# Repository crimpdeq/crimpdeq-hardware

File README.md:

# Crimpdeq Hardware

The Crimpdeq hardware is actively evolving. Several people have already built a prototype. Instructions for building your own prototype are available in the [Crimpdeq book](crimpdeq.github.io/book/). In parallel, I'm designing a PCB that is nearly finished but not yet manufactured, so it remains untested.

## Prototype

Here is the prototype:

The [Making Your Own Crimpdeq](https://crimpdeq.github.io/book/assembly.html) chapter explains the required materials and steps to build your own Crimpdeq.

## PCB

The PCB design is located under `hardware/crimpdeq/` and was created using KiCad. It is a two-layer board based on the [Rust ESP Board](https://github.com/esp-rs/esp-rust-board). This design removes unused sensors from the original board and adds the necessary components for this project.

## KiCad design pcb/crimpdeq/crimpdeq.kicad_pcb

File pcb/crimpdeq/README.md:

# Crimpdeq — 30 x 30 mm Four-Layer Design

This is the repository's single canonical PCB design and current production candidate. It
includes corrected ESP32 module grounding, an ADS1220 load-cell front-end, and compact
power/USB routing.

- Board/project/rules/schematic: `crimpdeq.{kicad_pcb,kicad_pro,kicad_dru,kicad_sch}`
- Outline: 30.00 x 30.00 mm (30.05 x 30.05 mm including edge stroke)
- Components: 55 total, 36 front / 19 back
- U1 antenna and D4 LED: back; J2 USB-C and U3 ADS1220: front
- U1 pins 37–53, including EPAD 49, are connected to GND as required by Espressif.
- R20/R21/R22 provide 10 kΩ pull-ups for SDA, SCL, and the MAX17048 alert output.
- U3 ADS1220 (TSSOP-16, LCSC C48263) uses ratiometric +3V3 excitation (E+/REFP0) with
  E-/REFN0 on GND. AVDD/DVDD decoupling is C11 + C19. R7/R8/C12 filter into AIN0/AIN1.
- SPI map: GPIO5 SCK, GPIO4 MOSI, GPIO3 CS, GPIO1 MISO (DOUT/~DRDY). CLK is grounded.
- The buck input, switch, output, and feedback components form a compact front-side cluster.
- Twelve dedicated GND stitching vias tie the outer floods to the solid L2 plane.
- All four load-cell pads (`E-`, `A-`, `A+`, `E+`) are together on the bottom edge near U3 and
  away from the antenna. `B+` and `SW` are on the right edge.
- The ESP32 antenna body overhangs the top edge; its all-layer copper keepout is retained.
- The USB-C housing overhangs the bottom edge by 1.00 mm; connector copper remains in-board.
- L2 is a signal-free GND plane. L3 carries the 3V3 pour and low-speed signals.
- KiCad error-level DRC: zero violations and zero unconnected items.
- Schematic ERC and PCB/schematic parity: zero errors.

Production files:

- Gerbers: `gerbers/crimpdeq.zip`
- Assembly package: `assembly/`

Manufacturer DFM review and physical validation of power integrity, USB, ADS1220 noise, antenna
performance, and connector fit remain required before production.

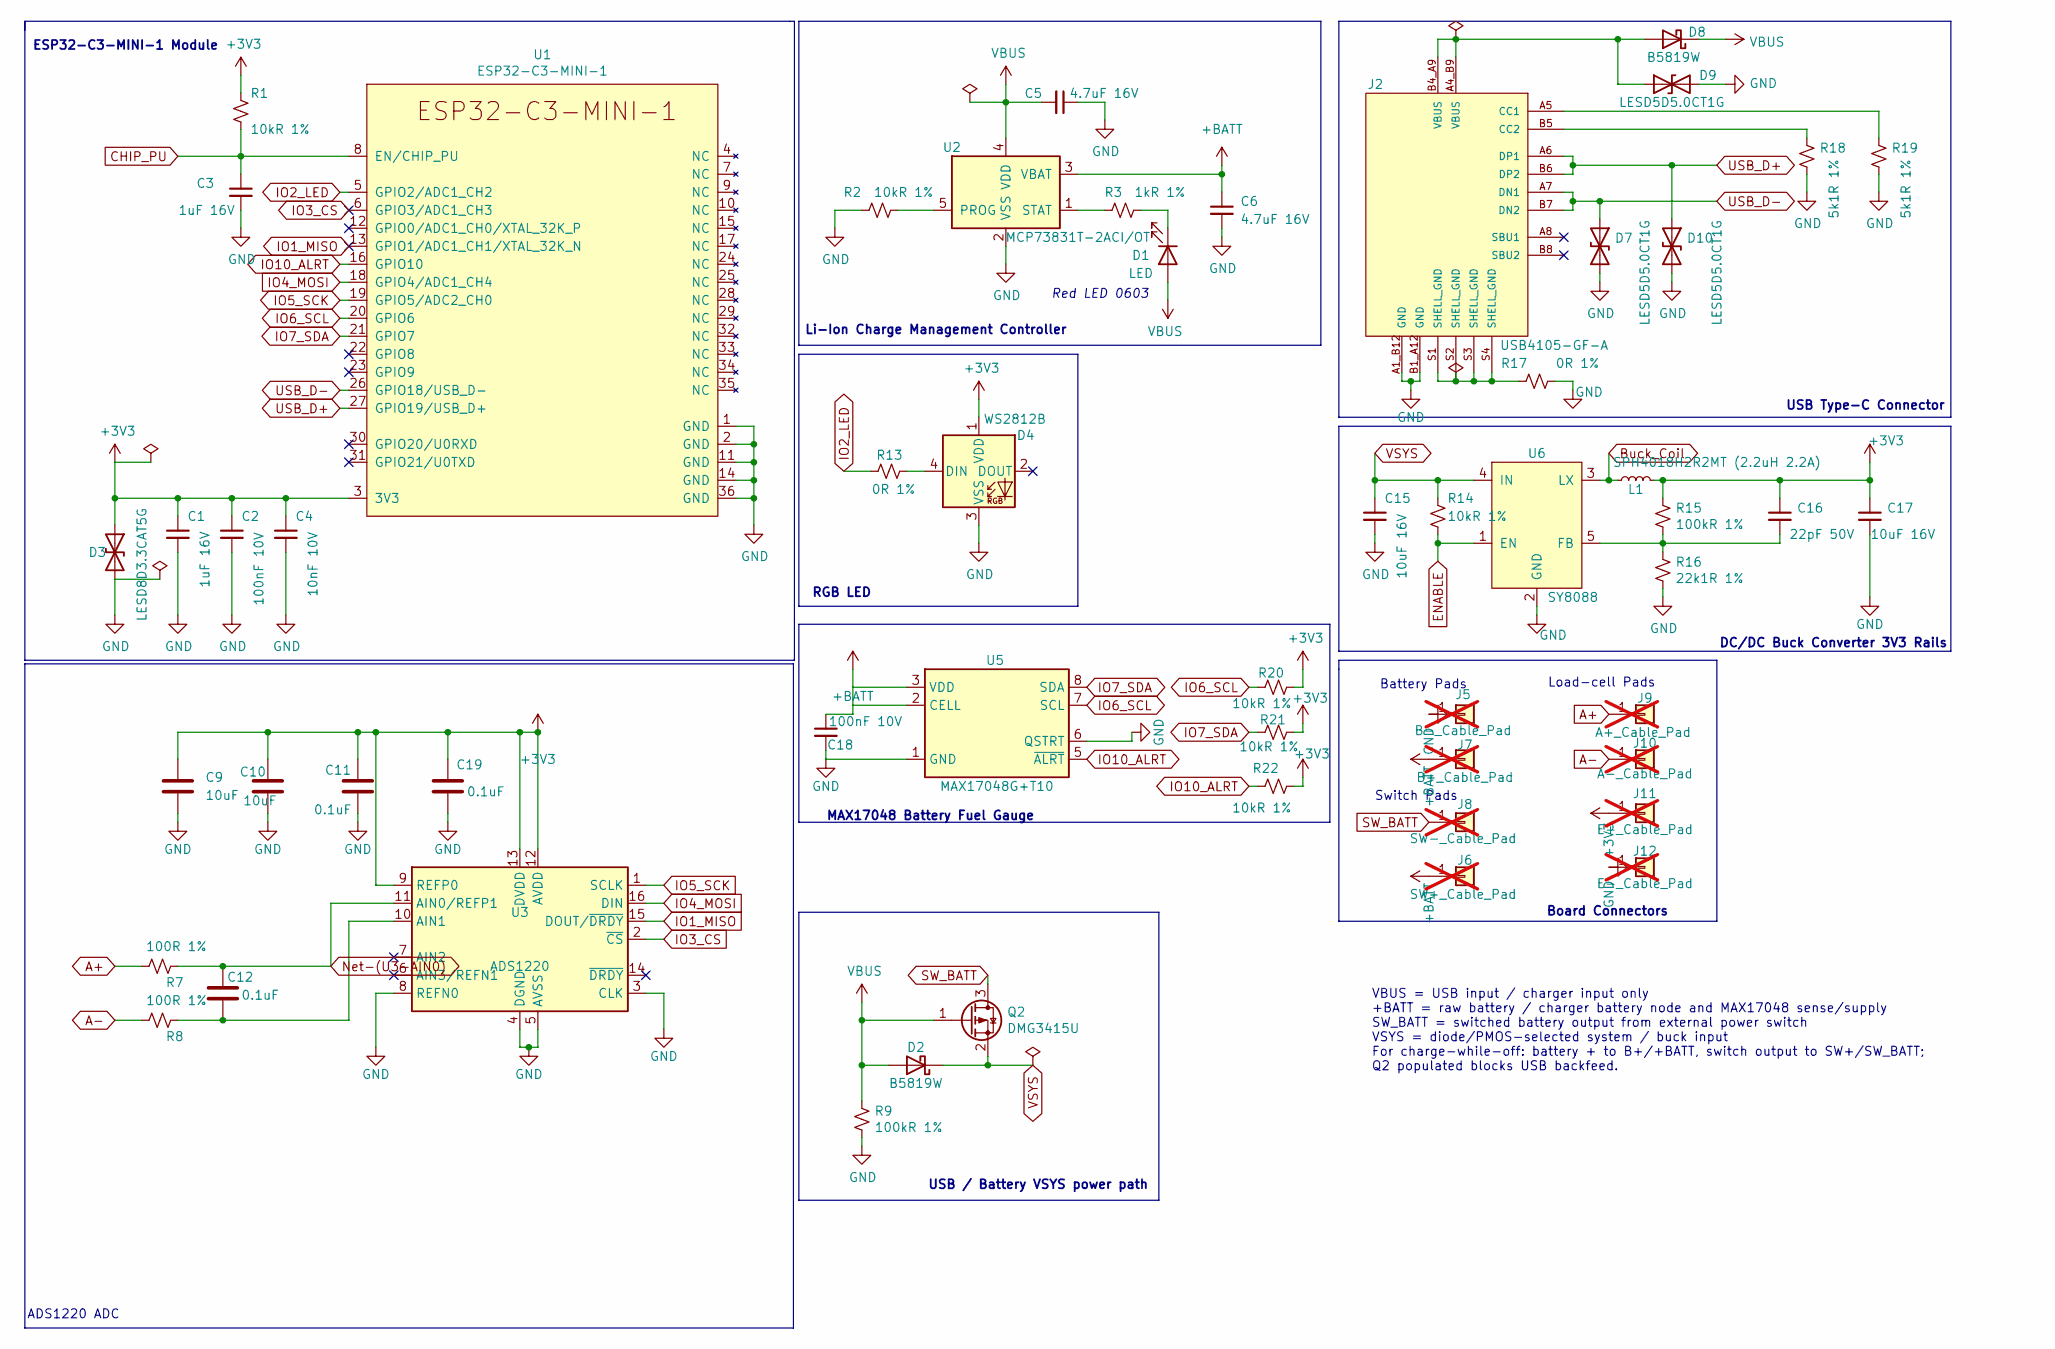
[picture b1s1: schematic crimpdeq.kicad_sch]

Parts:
C1, C3: 1uF 16V; C_0402_1005Metric; LCSC C52923
C2: 100nF 10V; C_0402_1005Metric; LCSC C1525
C4: 10nF 10V; C_0402_1005Metric; LCSC C15195
C5, C6: 4.7uF 16V; C_0603_1608Metric; LCSC C19666
C9, C10: 10uF; C_0603_1608Metric
C11, C12, C19: 0.1uF; C_0603_1608Metric
C15, C17: 10uF 16V; C_0805_2012Metric; LCSC C15850
C16: 22pF 50V; C_0603_1608Metric; LCSC C1653
C18: 100nF 10V; C_0402_1005Metric
D1: LED; LED_0603_1608Metric; LCSC C2286
D2, D8: B5819W; D_SOD-123; LCSC C8598
D3: LESD8D3.3CAT5G; D_SOD-882; LCSC C172409
D4: WS2812B; LED_WS2812B_PLCC4_5.0x5.0mm_P3.2mm
D7, D9, D10: LESD5D5.0CT1G; D_SOD-523; LCSC C383211
J2: USB4105-GF-A; GCT_USB4105-GF-A; PARTREV A3; LCSC C165948
J5: B-_Cable_Pad; TestPoint_THTPad_D1.5mm_Drill0.7mm; not fitted
J6: SW+_Cable_Pad; TestPoint_THTPad_D1.5mm_Drill0.7mm; not fitted
J7: B+_Cable_Pad; TestPoint_THTPad_D1.5mm_Drill0.7mm; not fitted
J8: SW-_Cable_Pad; TestPoint_THTPad_D1.5mm_Drill0.7mm; not fitted
J9: A+_Cable_Pad; TestPoint_THTPad_D1.5mm_Drill0.7mm; not fitted
J10: A-_Cable_Pad; TestPoint_THTPad_D1.5mm_Drill0.7mm; not fitted
J11: E+_Cable_Pad; TestPoint_THTPad_D1.5mm_Drill0.7mm; not fitted
J12: E-_Cable_Pad; TestPoint_THTPad_D1.5mm_Drill0.7mm; not fitted
L1: SPH4018H2R2MT (2.2uH 2.2A); L_Bourns-SRN4018; LCSC C370436
Q2: DMG3415U; SOT-23; LCSC C96616
R1, R2, R14: 10kR 1%; R_0402_1005Metric; LCSC C25744
R3: 1kR 1%; R_0402_1005Metric; LCSC C11702
R7, R8: 100R 1%; R_0402_1005Metric; LCSC C25076
R9, R15: 100kR 1%; R_0402_1005Metric; LCSC C25741
R13: 0R 1%; R_0402_1005Metric; LCSC C25744
R16: 22k1R 1%; R_0402_1005Metric; LCSC C43473
R17: 0R 1%; R_0402_1005Metric; LCSC C17168
R18, R19: 5k1R 1%; R_0402_1005Metric; LCSC C25905
R20, R21, R22: 10kR 1%; R_0402_1005Metric; LCSC C60490
U1: ESP32-C3-MINI-1; LCSC C2838502
U2: MCP73831T-2ACI/OT; SOT-23-5; LCSC C424093
U3: ADS1220; TSSOP-16_4.4x5mm_P0.65mm
U5: MAX17048G+T10; TDFN-8-1EP_2x2mm_P0.5mm_EP0.8x1.2mm
U6: SY8088; SOT-23-5; LCSC C479072

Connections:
+3V3: C1.1, C2.1, C4.1, C9.1, C10.1, C11.1, C16.1, C17.1, C19.1, D3.1 (A1), D4.1 (VDD), J11.1, L1.2, R1.1, R15.1, R20.2, R21.2, R22.2, U1.3 (3V3), U3.9 (REFP0), U3.12 (AVDD), U3.13 (DVDD)
+BATT: C6.1, C18.1, J6.1 (Pin_1_1), J7.1 (Pin_1_1), U2.3 (VBAT), U5.2 (CELL), U5.3 (VDD)
A+: J9.1 (Pin_1_1), R7.2
A-: J10.1 (Pin_1_1), R8.2
Buck_Coil: L1.1, U6.3 (LX)
CHIP_PU: C3.1, R1.2, U1.8 (EN/CHIP_PU)
ENABLE: R14.2, U6.1 (EN)
GND: C1.2, C2.2, C3.2, C4.2, C5.1, C6.2, C9.2, C10.2, C11.2, C15.2, C17.2, C18.2, C19.2, D3.2 (A2), D4.3 (VSS), D7.2 (A2), D9.2 (A2), D10.2 (A2), J2.A1_B12 (GND), J2.B1_A12 (GND), J5.1 (Pin_1_1), J12.1, R2.1, R9.2, R16.2, R17.2, R18.2, R19.2, U1.1 (GND), U1.2 (GND), U1.11 (GND), U1.14 (GND), U1.36 (GND), U1.37 (GND), U1.38 (GND), U1.39 (GND), U1.40 (GND), U1.41 (GND), U1.42 (GND), U1.43 (GND), U1.44 (GND), U1.45 (GND), U1.46 (GND), U1.47 (GND), U1.48 (GND), U1.49 (GND), U1.50 (GND), U1.51 (GND), U1.52 (GND), U1.53 (GND), U2.2 (VSS), U3.3 (CLK), U3.4 (DGND), U3.5 (AVSS), U3.8 (REFN0), U5.1 (GND), U5.4 (GND), U5.6 (QSTRT), U5.9 (GND), U6.2 (GND)
IO1_MISO: U1.13 (GPIO1/ADC1_CH1/XTAL_32K_N), U3.15 (DOUT/~DRDY)
IO2_LED: R13.1, U1.5 (GPIO2/ADC1_CH2)
IO3_CS: U1.6 (GPIO3/ADC1_CH3), U3.2 (~CS)
IO4_MOSI: U1.18 (GPIO4/ADC1_CH4), U3.16 (DIN)
IO5_SCK: U1.19 (GPIO5/ADC2_CH0), U3.1 (SCLK)
IO6_SCL: R20.1, U1.20 (GPIO6), U5.7 (SDA)
IO7_SDA: R21.1, U1.21 (GPIO7), U5.8 (SCL)
IO10_ALRT: R22.1, U1.16 (GPIO10), U5.5 (~ALRT)
unnamed: D1.1 (K), R3.2
unnamed: D4.4 (DIN), R13.2
unnamed: D8.2 (A), D9.1 (A1), J2.A4_B9 (VBUS), J2.B4_A9 (VBUS)
unnamed: J2.A5 (CC1), R19.1
unnamed: J2.B5 (CC2), R18.1
unnamed: J2.S1 (SHELL_GND), J2.S2 (SHELL_GND), J2.S3 (SHELL_GND), J2.S4 (SHELL_GND), R17.1
unnamed: R2.2, U2.5 (PROG)
unnamed: R3.1, U2.1 (STAT)
unnamed: C12.1, R7.1, U3.11 (AIN0/REFP1)
unnamed: C12.2, R8.1, U3.10 (AIN1)
unnamed: C16.2, R15.2, R16.1, U6.5 (FB)
SW_BATT: J8.1 (Pin_1_1), Q2.3 (D)
USB_D+: D10.1 (A1), J2.A6 (DP1), J2.B6 (DP2), U1.27 (GPIO19/USB_D+)
USB_D-: D7.1 (A1), J2.A7 (DN1), J2.B7 (DN2), U1.26 (GPIO18/USB_D-)
VBUS: C5.2, D1.2 (A), D2.2 (A), D8.1 (K), Q2.1 (G), R9.1, U2.4 (VDD)
VSYS: C15.1, D2.1 (K), Q2.2 (S), R14.1, U6.4 (IN)

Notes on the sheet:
ADS1220 ADC
USB Type-C Connector
Board Connectors
Li-Ion Charge Management Controller
USB / Battery VSYS power path
MAX17048 Battery Fuel Gauge
Red LED 0603
Load-cell Pads
Switch Pads
ESP32-C3-MINI-1 Module
RGB LED
DC/DC Buck Converter 3V3 Rails
Battery Pads
VBUS = USB input / charger input only +BATT = raw battery / charger battery node and MAX17048 sense/supply SW_BATT = switched battery output from external power switch VSYS = diode/PMOS-selected system / buck input For charge-while-off: battery + to B+/+BATT, switch output to SW+/SW_BATT; Q2 popula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

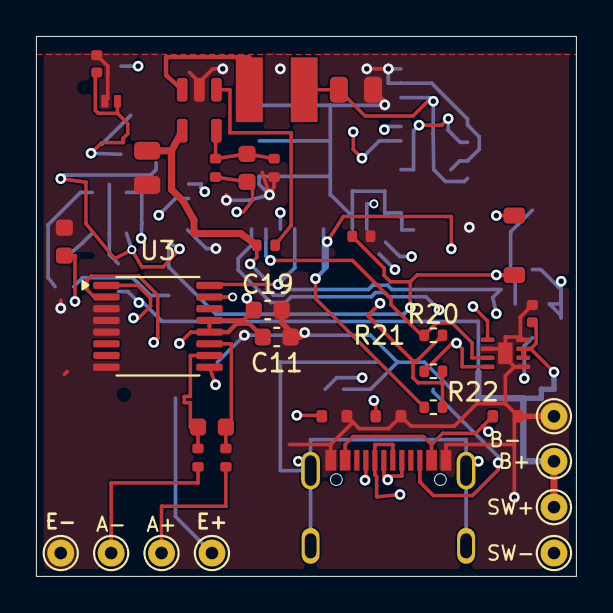
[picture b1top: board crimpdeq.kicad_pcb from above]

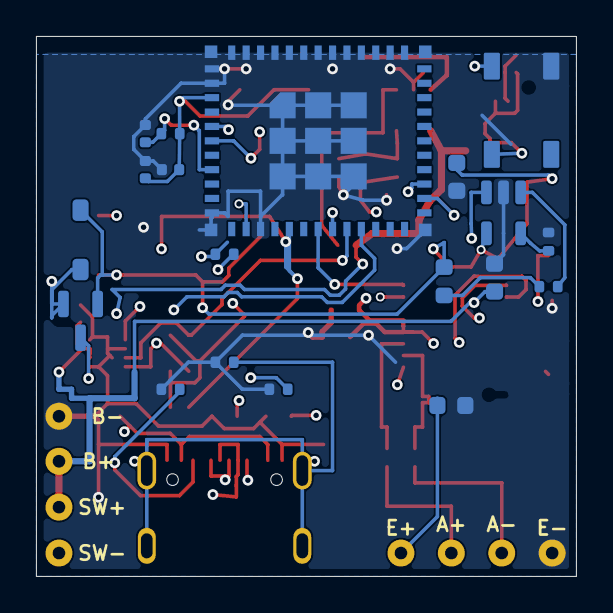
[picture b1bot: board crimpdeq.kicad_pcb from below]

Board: 4 copper layers, 30.0 x 30.0 mm, 55 parts (19 on the bottom side), 32 nets.

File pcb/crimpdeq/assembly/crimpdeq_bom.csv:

Item,Quantity,Designator,Value,Footprint,MPN,Type,Notes
1,2,"C1,C3",1uF 16V,C_0402_1005Metric,C52923,SMD,
2,2,"C2,C18",100nF 10V,C_0402_1005Metric,C1525,SMD,
3,1,C4,10nF 10V,C_0402_1005Metric,C15195,SMD,
4,2,"C5,C6",4.7uF 16V,C_0603_1608Metric,C19666,SMD,
5,2,"C9,C10",10uF,C_0603_1608Metric,C19702,SMD,
6,3,"C11,C12,C19",0.1uF,C_0603_1608Metric,C14663,SMD,
7,2,"C15,C17",10uF 16V,C_0805_2012Metric,C15850,SMD,
8,1,C16,22pF 50V,C_0603_1608Metric,C1653,SMD,
9,1,D1,LED,LED_0603_1608Metric,C2286,SMD,
10,2,"D2,D8",B5819W,D_SOD-123,C8598,SMD,
11,1,D3,LESD8D3.3CAT5G,D_SOD-882,C172409,SMD,
12,1,D4,WS2812B,LED_WS2812B_PLCC4_5.0x5.0mm_P3.2mm,C52917433,SMD,
13,3,"D7,D9,D10",LESD5D5.0CT1G,D_SOD-523,C2982332,SMD,
14,1,J2,USB4105-GF-A,GCT_USB4105-GF-A,C165948,Hybrid,PTH shell tabs; THT/manual soldering
15,1,J5,B-_Cable_Pad,TestPoint_THTPad_D1.5mm_Drill0.7mm,,THT,Do Not Place
16,1,J6,SW+_Cable_Pad,TestPoint_THTPad_D1.5mm_Drill0.7mm,,THT,Do Not Place
17,1,J7,B+_Cable_Pad,TestPoint_THTPad_D1.5mm_Drill0.7mm,,THT,Do Not Place
18,1,J8,SW-_Cable_Pad,TestPoint_THTPad_D1.5mm_Drill0.7mm,,THT,Do Not Place
19,1,J9,A+_Cable_Pad,TestPoint_THTPad_D1.5mm_Drill0.7mm,,THT,Do Not Place
20,1,J10,A-_Cable_Pad,TestPoint_THTPad_D1.5mm_Drill0.7mm,,THT,Do Not Place
21,1,J11,E+_Cable_Pad,TestPoint_THTPad_D1.5mm_Drill0.7mm,,THT,Do Not Place
22,1,J12,E-_Cable_Pad,TestPoint_THTPad_D1.5mm_Drill0.7mm,,THT,Do Not Place
23,1,L1,SPH4018H2R2MT (2.2uH 2.2A),L_Bourns-SRN4018,C370436,SMD,
24,1,Q2,DMG3415U,SOT-23,C96616,SMD,
25,6,"R1,R2,R14,R20,R21,R22",10kR 1%,R_0402_1005Metric,C60490,SMD,
26,1,R3,1kR 1%,R_0402_1005Metric,C11702,SMD,
27,2,"R7,R8",100R 1%,R_0402_1005Metric,C25076,SMD,
28,2,"R9,R15",100kR 1%,R_0402_1005Metric,C25741,SMD,
29,2,"R13,R17",0R 1%,R_0402_1005Metric,C17168,SMD,
30,1,R16,22k1R 1%,R_0402_1005Metric,C43473,SMD,
31,2,"R18,R19",5k1R 1%,R_0402_1005Metric,C25905,SMD,
32,1,U1,ESP32-C3-MINI-1,ESP32-C3-MINI-1,C2838502,SMD,
33,1,U2,MCP73831T-2ACI/OT,SOT-23-5,C424093,SMD,
34,1,U3,ADS1220,TSSOP-16_4.4x5mm_P0.65mm,C48263,SMD,
35,1,U5,MAX17048G+T10,TDFN-8-1EP_2x2mm_P0.5mm_EP0.8x1.2mm,C2682616,SMD,
36,1,U6,SY8088,SOT-23-5,C479072,SMD,

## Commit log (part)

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2025-12-30 feat: Initial commit
2025-12-30 chore: Create LICENSE-APACHE
2025-12-30 Create LICENSE-MIT
2025-12-30 docs: Create FUNDING.yml
